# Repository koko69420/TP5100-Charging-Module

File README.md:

# TP5100 Micro Li-Ion Battery Charging Module (V2 — Micro Redesign)

An ultra-compact, high-efficiency lithium-ion battery charging module based on the **TP5100** synchronous buck switching controller, designed in KiCad with full schematic, layer plots, and 3D photorealistic visualization.

> [!NOTE]
> **Project Context (V2 Micro Redesign)**  
> This board represents the **Micro Module redesign (August 2026)** of the author's original TP5100 charging board. It achieves an aggressive **66% reduction in surface area** (down to just 20.0 mm × 16.5 mm) compared to the original [**TP5100 1S Learning Design (V1)**](https://github.com/koko69420/TP5100-1S-Charger), while adding selectable 1S (4.2V) or 2S (8.4V) cell configuration, rounded corner edge cuts, and high-density double-sided SMD placement.

---

## 3D Renders

| Top View | Bottom View |
| :---: | :---: |
|  |  |

---

## Evolution & Version Comparison

| Parameter | [V1: KiCad Learning Board](https://github.com/koko69420/TP5100-1S-Charger) | V2: Micro Module Redesign (This Repo) |
| :--- | :--- | :--- |
| **Role & Context** | Initial design created to learn KiCad | Ultra-compact miniaturized redesign |
| **Board Dimensions** | 55.5 mm × 17.6 mm (977 mm²) | **20.0 mm × 16.5 mm** (330 mm²) — *66% smaller* |
| **Edge Geometry** | Standard rectangular (90° corners) | **Rounded corner arcs** |
| **Battery Topology** | 1S dedicated (4.2V) | **1S (4.2V) / 2S (8.4V) selectable** via solder jumper |
| **Max Charge Current** | Up to 2.0 A | Up to 2.0 A |
| **Input Supply** | 5.0 V – 18.0 V DC | 5.0 V – 18.0 V DC |
| **Component Density** | Spacious layout for hand assembly | **High-density double-sided SMD** layout |
| **Thermal Strategy** | Distributed copper pours | **Thermal relief via stitching under IC** |

---

## Features

- **Ultra-Compact Micro Form Factor**:
  - Footprint reduced to only 20.0 mm × 16.5 mm with rounded corners, suitable for embedding inside tight handheld enclosures, RC models, and modular battery packs.
- **Selectable 1S / 2S Charging**:
  - Configurable for 1-cell (4.2V) or 2-cell series (8.4V) lithium-ion / lithium-polymer chemistry via onboard solder jumper.
- **Synchronous Buck Switching Architecture**:
  - High switching frequency (~400 kHz) allows use of small surface-mount power inductors while maintaining cool operation at up to 2A charge current.
  - Multi-stage Constant Current (CC) / Constant Voltage (CV) charging with trickle pre-charging for over-discharged cells.
- **Wide Input Supply Range**:
  - 5V to 18V DC input capability, compatible with USB supplies, 12V DC power adapters, and small solar panels.
- **Dual Status Indication & Telemetry**:
  - Onboard dual LED indicators for active charging state and charge completion / battery standby.
- **Comprehensive Visual Documentation**:
  - Multi-layer vector assembly plots (`pcb.pdf`, `TP5100_Charging_Module-F_Cu.pdf`, `TP5100_Charging_Module-B_Cu.pdf`).
  - High-resolution schematic diagrams (`Schematic.pdf`, `Schematic.png`).
  - Front and back photorealistic 3D board renders (`Front.png`, `Back.png`).

---

## Hardware Specification

| Parameter | Specification | Details |
| :--- | :--- | :--- |
| **Controller IC** | TP5100 | Synchronous Step-Down Lithium Battery Charger |
| **Input Supply** | 5.0 V – 18.0 V DC | DC barrel jacks, USB-C 5V–12V PD, solar panels |
| **Output Voltage** | 4.2V (1S) / 8.4V (2S)| Solder-jumper selectable |
| **Max Charge Current**| 2.0 A | Current programming resistor dependent |
| **Switching Freq** | ~400 kHz | High-frequency operation for miniature power inductors |
| **Board Dimensions** | 20.0 mm × 16.5 mm | Double-sided 2-layer FR4 with rounded corners |

---

## Project Structure

```text
TP5100-Charging-Module/
├── Front.png                         # 3D PCB top surface render
├── Back.png                          # 3D PCB bottom surface render
├── Schematic.pdf                     # High-resolution vector schematic
├── Schematic.png                     # Raster schematic preview
├── pcb.pdf                           # Complete board outline and trace plots
├── TP5100_Charging_Module.kicad_sch  # KiCad schematic design file
├── TP5100_Charging_Module.kicad_pcb  # KiCad PCB board layout
├── TP5100_Charging_Module.kicad_pro  # KiCad project file
├── TP5100_Charging_Module-F_Cu.pdf   # Front copper layer plot
├── TP5100_Charging_Module-B_Cu.pdf   # Back copper layer plot
├── .gitignore                        # Git ignore patterns
└── README.md                         # Project documentation
```

---

## License

Open hardware design. All rights reserved by Kausthubh Viswanath.

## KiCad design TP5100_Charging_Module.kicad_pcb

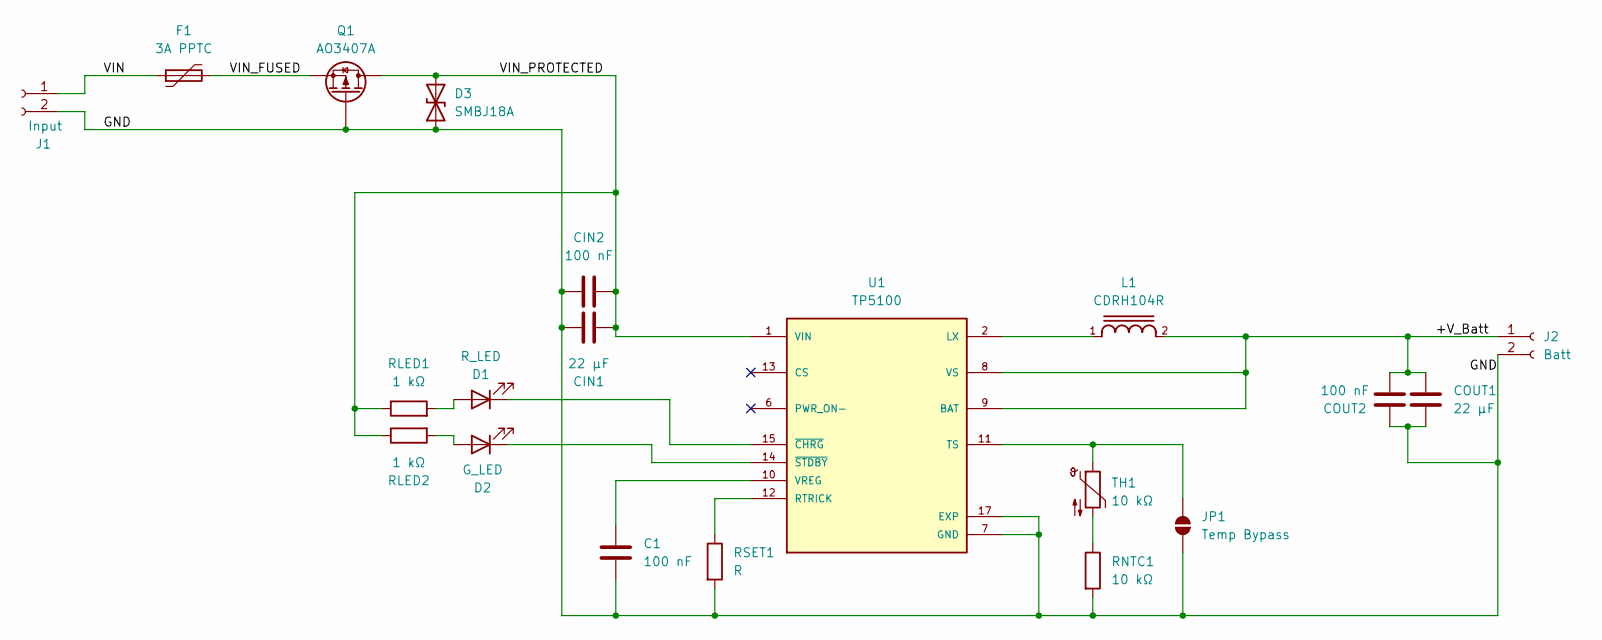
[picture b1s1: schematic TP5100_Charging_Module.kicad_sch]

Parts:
C1: 100 nF; C_1206_3216Metric
CIN1: 22 µF; C_1206_3216Metric
CIN2: 100 nF; C_1206_3216Metric
COUT1: 22 µF; C_1206_3216Metric
COUT2: 100 nF; C_1206_3216Metric
D1: R_LED; LED_0603_1608Metric
D2: G_LED; LED_0603_1608Metric
D3: SMBJ18A; D_SMB
F1: 3A PPTC; Fuse_1206_3216Metric
J1: Input; SolderWire-0.5sqmm_1x02_P4.8mm_D0.9mm_OD2.3mm
J2: Batt; SolderWire-0.5sqmm_1x02_P4.8mm_D0.9mm_OD2.3mm
JP1: Temp Bypass; SolderJumper-2_P1.3mm_Open_TrianglePad1.0x1.5mm
L1: CDRH104R
Q1: AO3407A; SOT-23-3
RLED1, RLED2: 1 kΩ; R_0805_2012Metric
RNTC1: 10 kΩ; R_0805_2012Metric
RSET1: R; R_0805_2012Metric
TH1: 10 kΩ; R_Axial_DIN0204_L3.6mm_D1.6mm_P2.54mm_Vertical
U1: TP5100; QFN65P400X400X90-17N; PARTREV 2.3

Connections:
/+V_Batt: COUT1.2, COUT2.2, J2.1, L1.2, U1.8 (VS), U1.9 (BAT)
/GND: C1.2, CIN1.1, CIN2.1, COUT1.1, COUT2.1, D3.1 (A1), J1.2, J2.2, JP1.1 (A), Q1.2 (G), RNTC1.2, RSET1.2, U1.7 (GND), U1.17 (EXP); also elsewhere on the board
/VIN: F1.1, J1.1
/VIN_FUSED: F1.2, Q1.1 (S)
/VIN_PROTECTED: CIN1.2, CIN2.2, D3.2 (A2), Q1.3 (D), RLED1.1, RLED2.1, U1.1 (VIN), U1.4 (VIN), U1.5 (VIN), U1.16 (VIN)
unnamed: D1.2 (A), RLED1.2
unnamed: D1.1 (K), U1.15 (~CHRG)
unnamed: D2.2 (A), RLED2.2
unnamed: D2.1 (K), U1.14 (~STDBY)
unnamed 9: JP1.2 (B), TH1.1, U1.11 (TS); also elsewhere on the board
unnamed: L1.1, U1.2 (LX), U1.3 (LX)
unnamed 11: RNTC1.1, TH1.2; also elsewhere on the board
unnamed 12: RSET1.1, U1.12 (RTRICK); also elsewhere on the board
unnamed: C1.1, U1.10 (VREG)

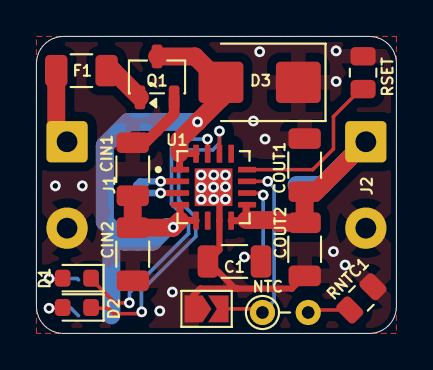
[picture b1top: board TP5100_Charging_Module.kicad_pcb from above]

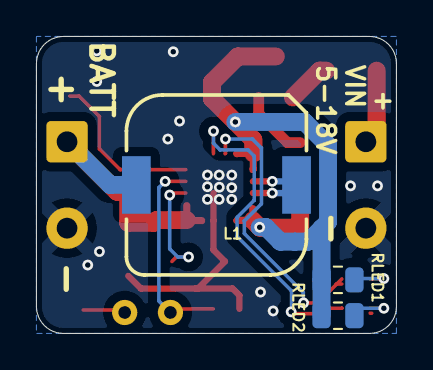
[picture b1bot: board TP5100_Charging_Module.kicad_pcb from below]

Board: 2 copper layers, 20.0 x 16.5 mm, 20 parts (3 on the bottom side), 14 nets.

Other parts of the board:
NTC: 10 kΩ; R_Axial_DIN0204_L3.6mm_D1.6mm_P2.54mm_Vertical
RSET: R; R_0805_2012Metric

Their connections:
/GND: RSET.2; also elsewhere on the board
unnamed 9: NTC.1; also elsewhere on the board
unnamed 11: NTC.2; also elsewhere on the board
unnamed 12: RSET.1; also elsewhere on the board
